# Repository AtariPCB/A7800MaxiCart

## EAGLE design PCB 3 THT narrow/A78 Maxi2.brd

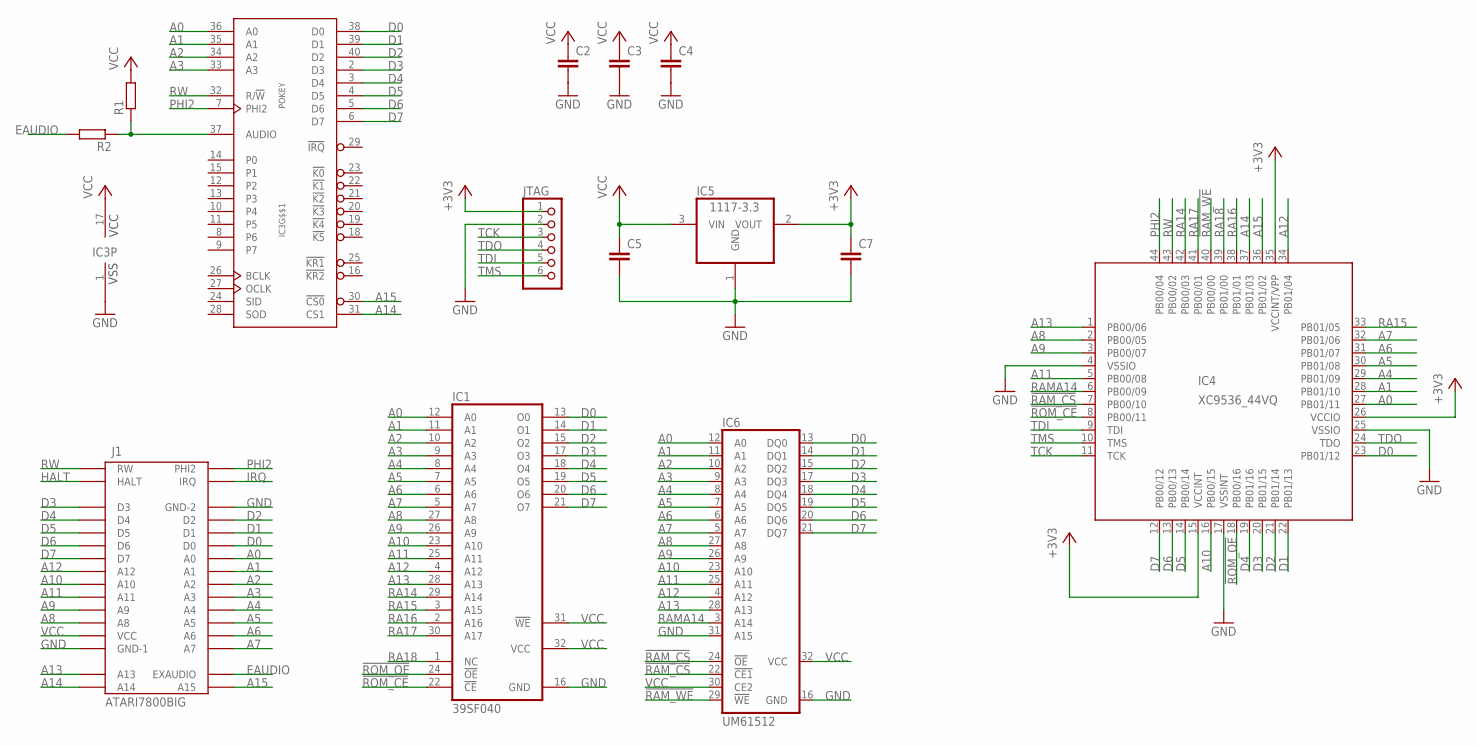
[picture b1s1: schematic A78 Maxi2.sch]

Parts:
C2: C-EU025-025X050; C025-025X050
C3, C4, C5, C7: C-EUC0805; C0805
IC1: 39SF040; DIL32
IC3: POKEY; DIL40
IC4: XC9536_44VQ; SQFP-S-10X10-44
IC5: 1117-3.3; SOT223
IC6: UM61512; DIL32-NARROW
J1: ATARI7800BIG; ATARI-7800-BIG
JTAG: PINHD-1X6; 1X06
R1, R2: R-EU_R0805; R0805

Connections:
!RAM_CS: IC4.7 (PB00/10), IC6.22 (!CE1), IC6.24 (!OE)
!RAM_WE: IC4.40 (PB00/00), IC6.29 (!WE)
!ROM_CE: IC1.22 (!CE), IC4.8 (PB00/11)
!ROM_OE: IC1.24 (!OE), IC4.18 (PB00/16)
+3V3: C7.1, IC4.15 (VCCINT), IC4.26 (VCCIO), IC4.35 (VCCINT/VPP), IC5.2 (VOUT), JTAG.1
A0: IC1.12 (A0), IC3.36 (A0), IC4.27 (PB01/11), IC6.12 (A0), J1.26 (A0)
A1: IC1.11 (A1), IC3.35 (A1), IC4.28 (PB01/10), IC6.11 (A1), J1.25 (A1)
A2: IC1.10 (A2), IC3.34 (A2), IC6.10 (A2), J1.24 (A2)
A3: IC1.9 (A3), IC3.33 (A3), IC6.9 (A3), J1.23 (A3)
A4: IC1.8 (A4), IC4.29 (PB01/09), IC6.8 (A4), J1.22 (A4)
A5: IC1.7 (A5), IC4.30 (PB01/08), IC6.7 (A5), J1.21 (A5)
A6: IC1.6 (A6), IC4.31 (PB01/07), IC6.6 (A6), J1.20 (A6)
A7: IC1.5 (A7), IC4.32 (PB01/06), IC6.5 (A7), J1.19 (A7)
A8: IC1.27 (A8), IC4.2 (PB00/05), IC6.27 (A8), J1.12 (A8)
A9: IC1.26 (A9), IC4.3 (PB00/07), IC6.26 (A9), J1.11 (A9)
A10: IC1.23 (A10), IC4.16 (PB00/15), IC6.23 (A10), J1.9 (A10)
A11: IC1.25 (A11), IC4.5 (PB00/08), IC6.25 (A11), J1.10 (A11)
A12: IC1.4 (A12), IC4.34 (PB01/04), IC6.4 (A12), J1.8 (A12)
A13: IC1.28 (A13), IC4.1 (PB00/06), IC6.28 (A13), J1.15 (A13)
A14: IC3.31 (CS1), IC4.37 (PB01/03), J1.16 (A14)
A15: IC3.30 (!CS0), IC4.36 (PB01/02), J1.17 (A15)
D0: IC1.13 (O0), IC3.38 (D0), IC4.23 (PB01/12), IC6.13 (DQ0), J1.27 (D0)
D1: IC1.14 (O1), IC3.39 (D1), IC4.22 (PB01/13), IC6.14 (DQ1), J1.28 (D1)
D2: IC1.15 (O2), IC3.40 (D2), IC4.21 (PB01/14), IC6.15 (DQ2), J1.29 (D2)
D3: IC1.17 (O3), IC3.2 (D3), IC4.20 (PB01/15), IC6.17 (DQ3), J1.3 (D3)
D4: IC1.18 (O4), IC3.3 (D4), IC4.19 (PB01/16), IC6.18 (DQ4), J1.4 (D4)
D5: IC1.19 (O5), IC3.4 (D5), IC4.14 (PB00/14), IC6.19 (DQ5), J1.5 (D5)
D6: IC1.20 (O6), IC3.5 (D6), IC4.13 (PB00/13), IC6.20 (DQ6), J1.6 (D6)
D7: IC1.21 (O7), IC3.6 (D7), IC4.12 (PB00/12), IC6.21 (DQ7), J1.7 (D7)
EAUDIO: J1.18 (EXAUDIO), R2.2
GND: C2.2, C3.2, C4.2, C5.2, C7.2, IC1.16 (GND), IC3.1 (VSS), IC4.4 (VSSIO), IC4.17 (VSSINT), IC4.25 (VSSIO), IC5.1 (GND), IC6.16 (GND), IC6.31 (A15), J1.14 (GND-1), J1.30 (GND-2), JTAG.2
HALT: J1.2 (HALT)
IRQ: J1.31 (IRQ)
unnamed: IC3.37 (AUDIO), R1.1, R2.1
PHI2: IC3.7 (PHI2), IC4.44 (PB00/04), J1.32 (PHI2)
RA14: IC1.29 (A14), IC4.42 (PB00/03)
RA15: IC1.3 (A15), IC4.33 (PB01/05)
RA16: IC1.2 (A16), IC4.38 (PB01/01)
RA17: IC1.30 (A17), IC4.41 (PB00/01)
RA18: IC1.1 (NC), IC4.39 (PB01/00)
RAMA14: IC4.6 (PB00/09), IC6.3 (A14)
RW: IC3.32 (R/!W), IC4.43 (PB00/02), J1.1 (RW)
TCK: IC4.11 (TCK), JTAG.3
TDI: IC4.9 (TDI), JTAG.5
TDO: IC4.24 (TDO), JTAG.4
TMS: IC4.10 (TMS), JTAG.6
VCC: C2.1, C3.1, C4.1, C5.1, IC1.31 (!WE), IC1.32 (VCC), IC3.17 (VCC), IC5.3 (VIN), IC6.30 (CE2), IC6.32 (VCC), J1.13 (VCC), R1.2

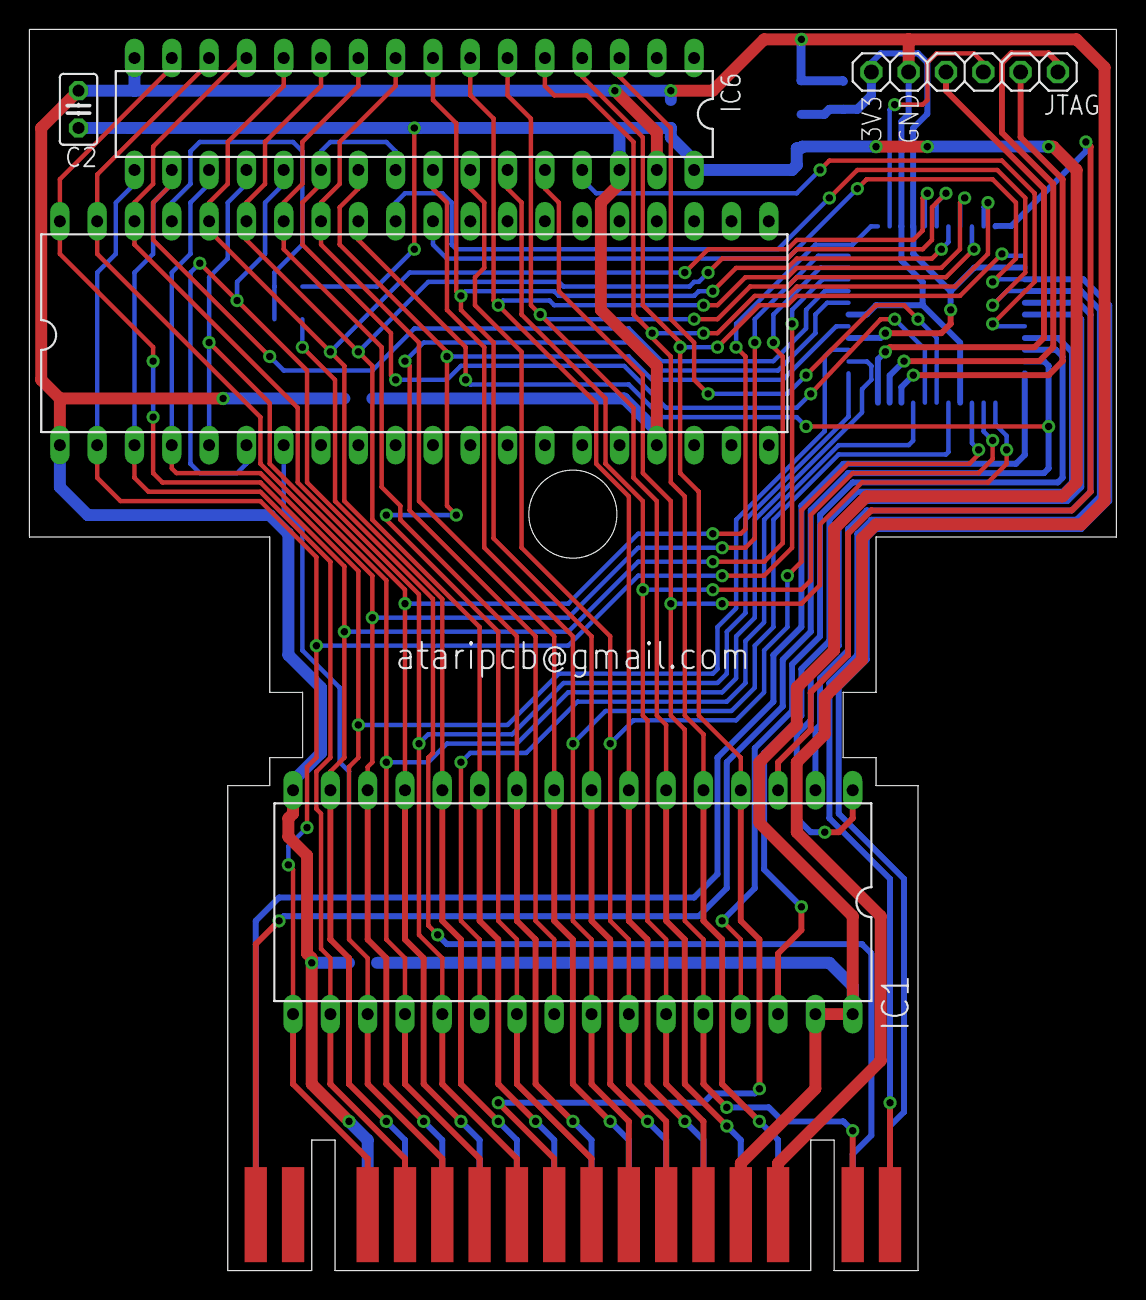
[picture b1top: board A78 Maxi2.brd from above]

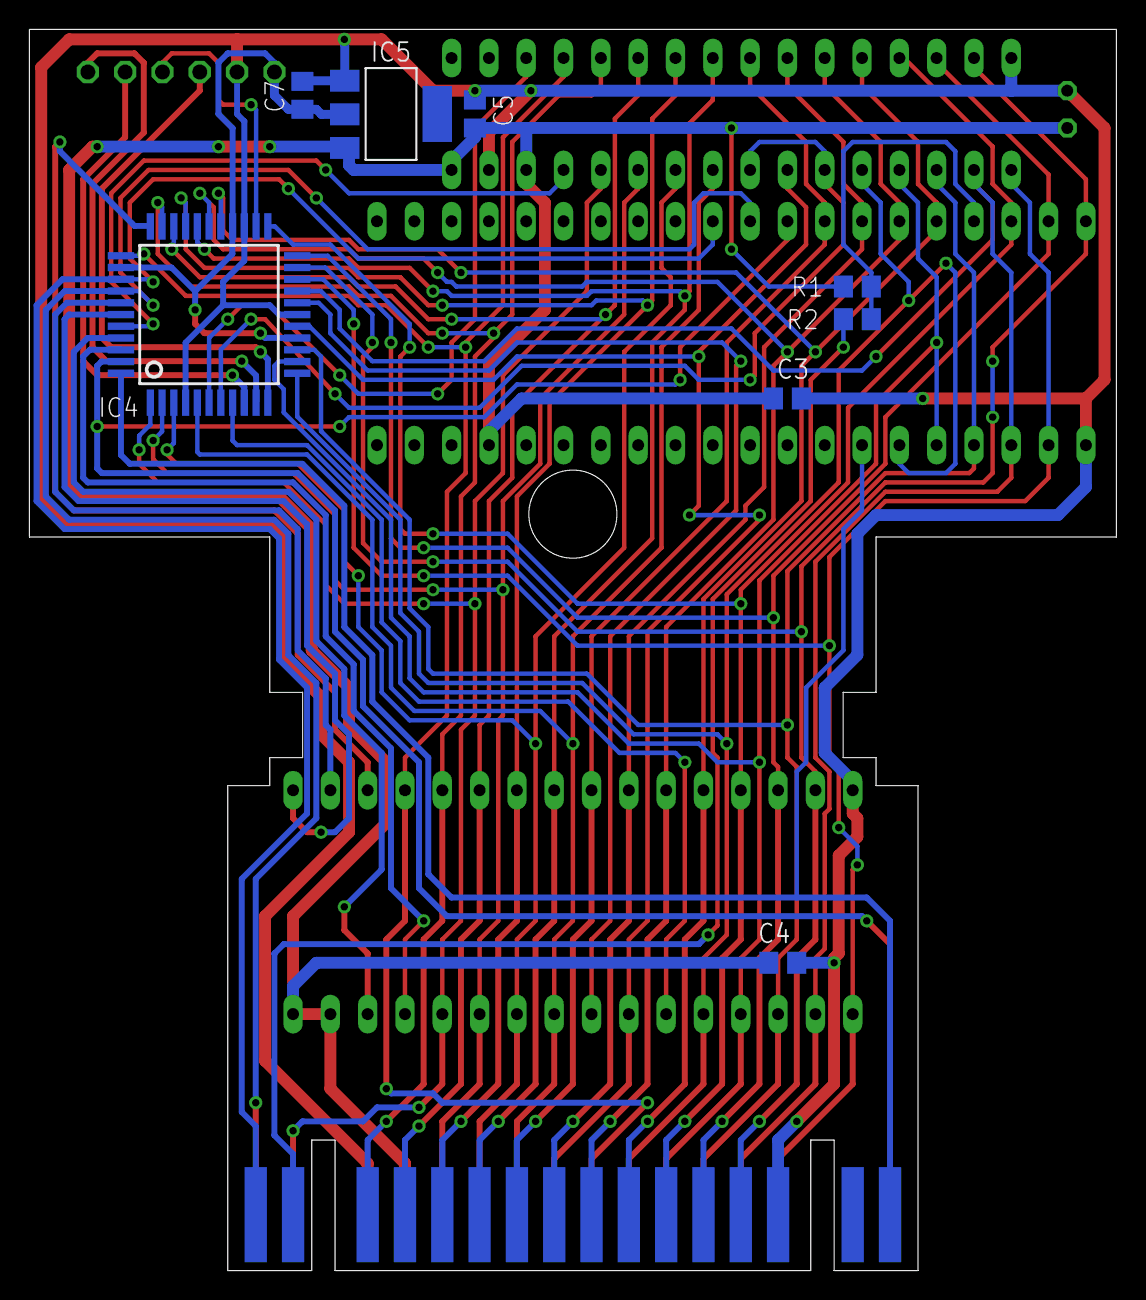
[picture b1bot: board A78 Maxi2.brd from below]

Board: 2 copper layers, 74.0 x 84.5 mm, 14 parts (8 on the bottom side), 45 nets.

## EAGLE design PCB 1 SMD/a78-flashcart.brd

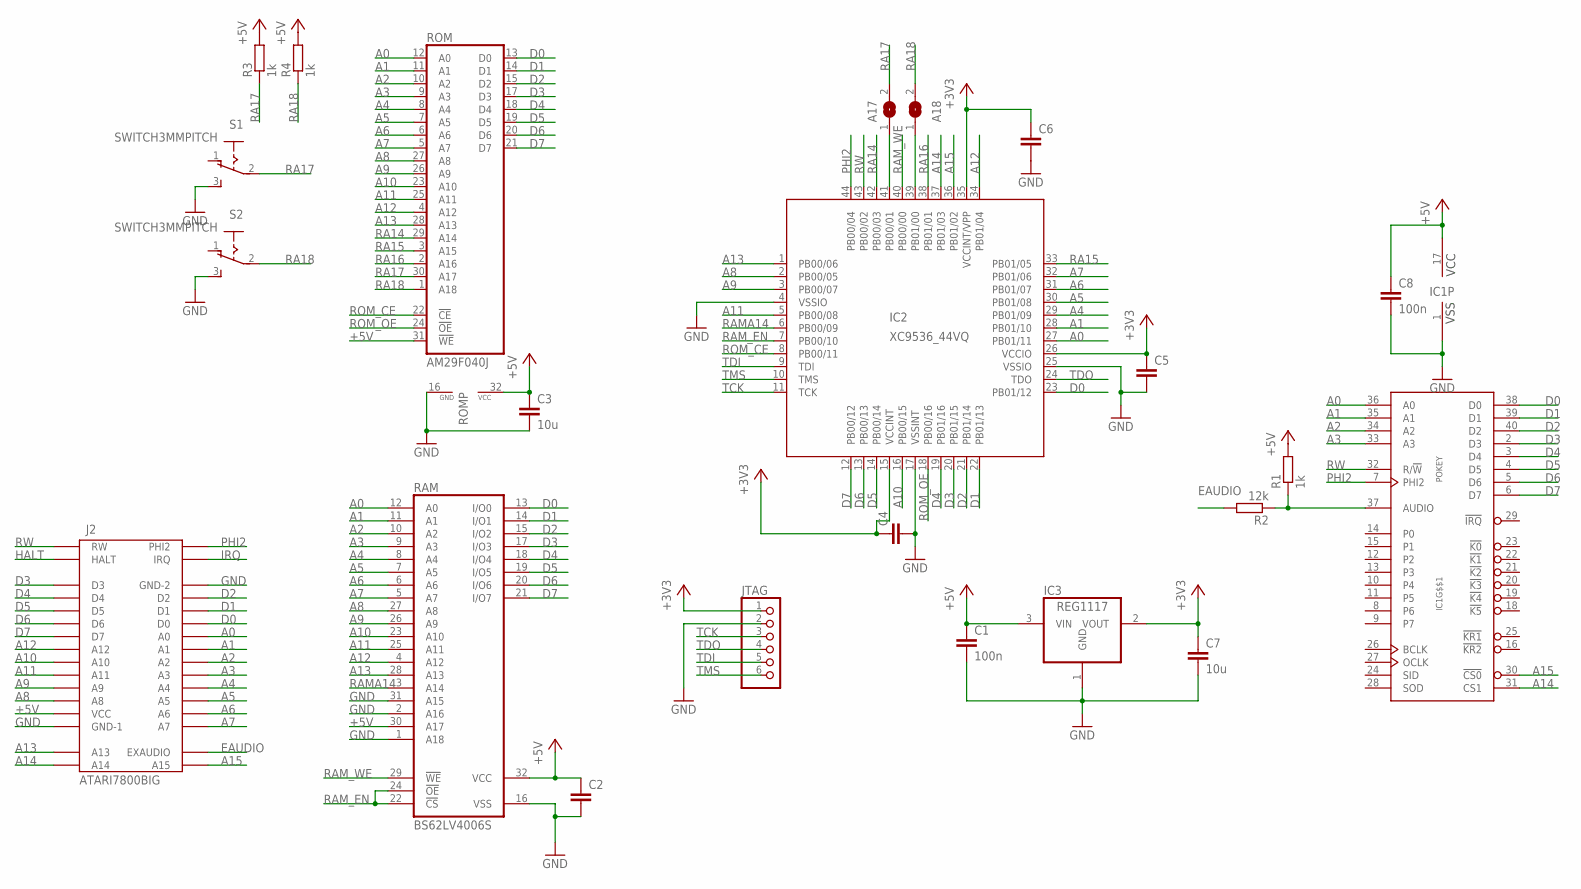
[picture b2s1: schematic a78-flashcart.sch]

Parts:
A17, A18: SJ
C1, C8: 100n; C0805
C2, C4, C5, C6: C-EUC0805; C0805
C3, C7: 10u; C0805
IC1: POKEY; DIL40
IC2: XC9536_44VQ; SQFP-S-10X10-44
IC3: REG1117; SOT223
J2: ATARI7800BIG; ATARI-7800-BIG
JTAG: PINHD-1X6; 1X06
R1, R3, R4: 1k; R0805
R2: 12k; R0805
RAM: BS62LV4006S; SOP-32
ROM: AM29F040J; PLCC32R
S1, S2: SWITCH3MMPITCH

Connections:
+3V3: C4.1, C5.1, C6.1, C7.1, IC2.15 (VCCINT), IC2.26 (VCCIO), IC2.35 (VCCINT/VPP), IC3.2 (VOUT), JTAG.1
+5V: C1.1, C2.1, C3.1, C8.1, IC1.17 (VCC), IC3.3 (VIN), J2.13 (VCC), R1.2, R3.2, R4.2, RAM.30 (A17), RAM.32 (VCC), ROM.31 (!WE), ROM.32 (VCC)
A0: IC1.36 (A0), IC2.27 (PB01/11), J2.26 (A0), RAM.12 (A0), ROM.12 (A0)
A1: IC1.35 (A1), IC2.28 (PB01/10), J2.25 (A1), RAM.11 (A1), ROM.11 (A1)
A2: IC1.34 (A2), J2.24 (A2), RAM.10 (A2), ROM.10 (A2)
A3: IC1.33 (A3), J2.23 (A3), RAM.9 (A3), ROM.9 (A3)
A4: IC2.29 (PB01/09), J2.22 (A4), RAM.8 (A4), ROM.8 (A4)
A5: IC2.30 (PB01/08), J2.21 (A5), RAM.7 (A5), ROM.7 (A5)
A6: IC2.31 (PB01/07), J2.20 (A6), RAM.6 (A6), ROM.6 (A6)
A7: IC2.32 (PB01/06), J2.19 (A7), RAM.5 (A7), ROM.5 (A7)
A8: IC2.2 (PB00/05), J2.12 (A8), RAM.27 (A8), ROM.27 (A8)
A9: IC2.3 (PB00/07), J2.11 (A9), RAM.26 (A9), ROM.26 (A9)
A10: IC2.16 (PB00/15), J2.9 (A10), RAM.23 (A10), ROM.23 (A10)
A11: IC2.5 (PB00/08), J2.10 (A11), RAM.25 (A11), ROM.25 (A11)
A12: IC2.34 (PB01/04), J2.8 (A12), RAM.4 (A12), ROM.4 (A12)
A13: IC2.1 (PB00/06), J2.15 (A13), RAM.28 (A13), ROM.28 (A13)
A14: IC1.31 (CS1), IC2.37 (PB01/03), J2.16 (A14)
A15: IC1.30 (!CS0), IC2.36 (PB01/02), J2.17 (A15)
D0: IC1.38 (D0), IC2.23 (PB01/12), J2.27 (D0), RAM.13 (I/O0), ROM.13 (D0)
D1: IC1.39 (D1), IC2.22 (PB01/13), J2.28 (D1), RAM.14 (I/O1), ROM.14 (D1)
D2: IC1.40 (D2), IC2.21 (PB01/14), J2.29 (D2), RAM.15 (I/O2), ROM.15 (D2)
D3: IC1.2 (D3), IC2.20 (PB01/15), J2.3 (D3), RAM.17 (I/O3), ROM.17 (D3)
D4: IC1.3 (D4), IC2.19 (PB01/16), J2.4 (D4), RAM.18 (I/O4), ROM.18 (D4)
D5: IC1.4 (D5), IC2.14 (PB00/14), J2.5 (D5), RAM.19 (I/O5), ROM.19 (D5)
D6: IC1.5 (D6), IC2.13 (PB00/13), J2.6 (D6), RAM.20 (I/O6), ROM.20 (D6)
D7: IC1.6 (D7), IC2.12 (PB00/12), J2.7 (D7), RAM.21 (I/O7), ROM.21 (D7)
EAUDIO: J2.18 (EXAUDIO), R2.2
GND: C1.2, C2.2, C3.2, C4.2, C5.2, C6.2, C7.2, C8.2, IC1.1 (VSS), IC2.4 (VSSIO), IC2.17 (VSSINT), IC2.25 (VSSIO), IC3.1 (GND), J2.14 (GND-1), J2.30 (GND-2), JTAG.2, RAM.1 (A18), RAM.2 (A16), RAM.16 (VSS), RAM.31 (A15), ROM.16 (GND), S1.3 (S), S2.3 (S)
HALT: J2.2 (HALT)
IRQ: J2.31 (IRQ)
unnamed: IC1.37 (AUDIO), R1.1, R2.1
unnamed: A17.1, IC2.41 (PB00/01)
unnamed: A18.1, IC2.39 (PB01/00)
PHI2: IC1.7 (PHI2), IC2.44 (PB00/04), J2.32 (PHI2)
RA14: IC2.42 (PB00/03), ROM.29 (A14)
RA15: IC2.33 (PB01/05), ROM.3 (A15)
RA16: IC2.38 (PB01/01), ROM.2 (A16)
RA17: A17.2, R3.1, ROM.30 (A17), S1.2
RA18: A18.2, R4.1, ROM.1 (A18), S2.2
RAMA14: IC2.6 (PB00/09), RAM.3 (A14)
RAM_EN: IC2.7 (PB00/10), RAM.22 (!CS), RAM.24 (!OE)
RAM_WE: IC2.40 (PB00/00), RAM.29 (!WE)
ROM_CE: IC2.8 (PB00/11), ROM.22 (!CE)
ROM_OE: IC2.18 (PB00/16), ROM.24 (!OE)
RW: IC1.32 (R/!W), IC2.43 (PB00/02), J2.1 (RW)
TCK: IC2.11 (TCK), JTAG.3
TDI: IC2.9 (TDI), JTAG.5
TDO: IC2.24 (TDO), JTAG.4
TMS: IC2.10 (TMS), JTAG.6

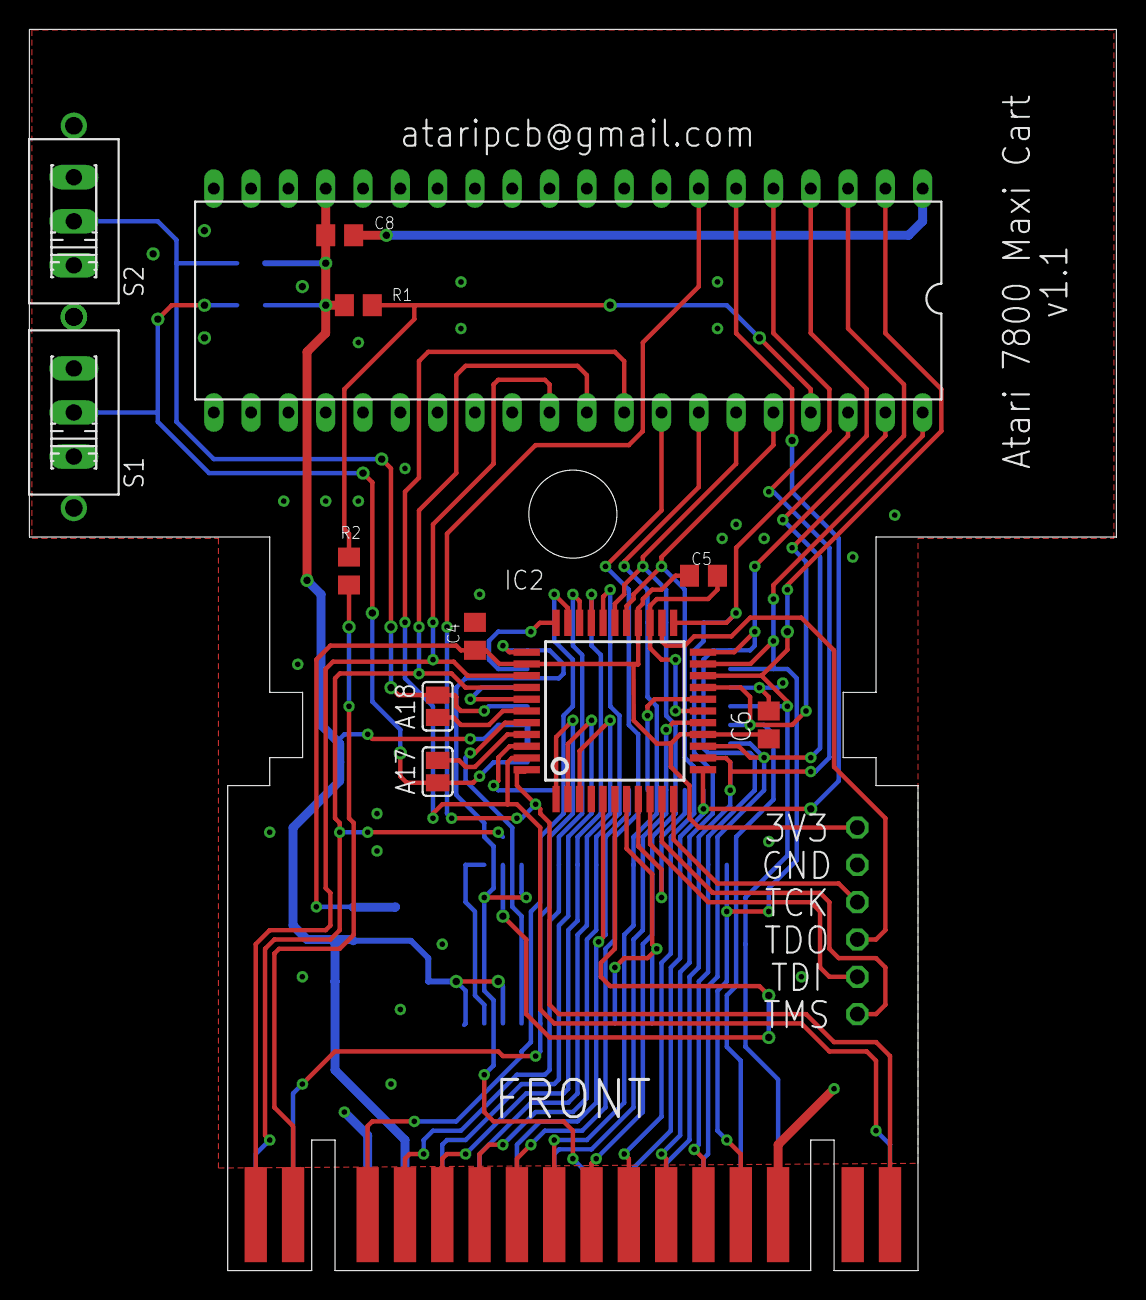
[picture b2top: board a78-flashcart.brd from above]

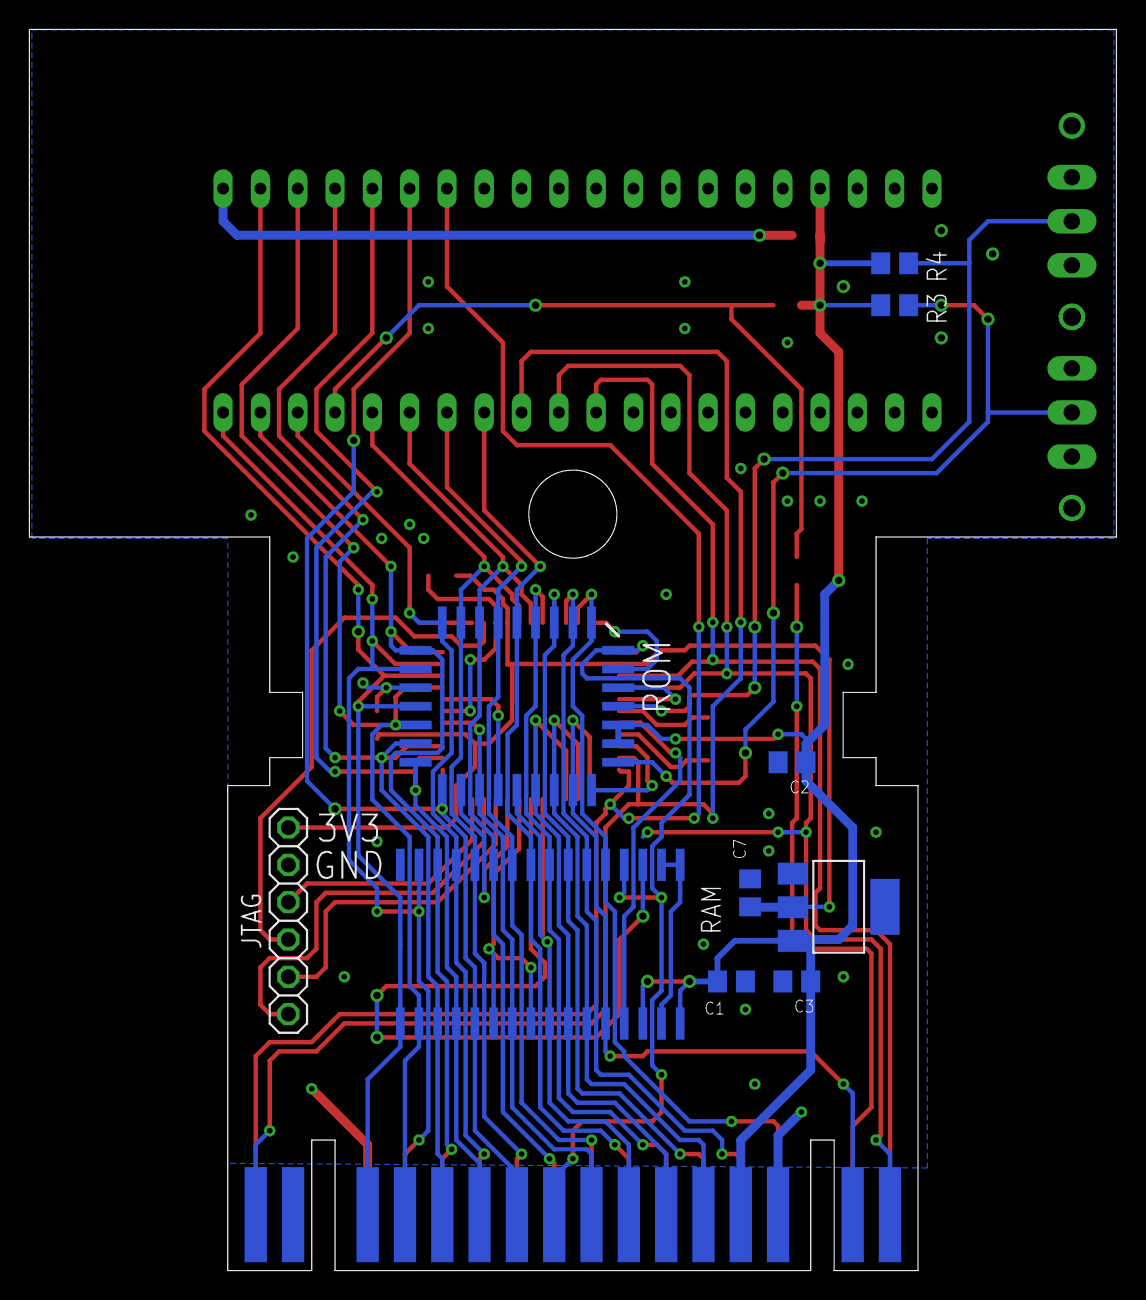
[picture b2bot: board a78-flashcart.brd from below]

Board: 2 copper layers, 74.0 x 84.5 mm, 23 parts (11 on the bottom side), 47 nets.

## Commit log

2025-07-22 Add files
2025-08-04 Remove files
2025-08-04 Rename
2025-08-05 File add

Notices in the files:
parts and their libraries:
eagle-6.5.0-atari: Copyright (c) 2010
Copyright (c) 2009
This library is licensed under the
Creative Commons Attribution 3.0 United States License.
